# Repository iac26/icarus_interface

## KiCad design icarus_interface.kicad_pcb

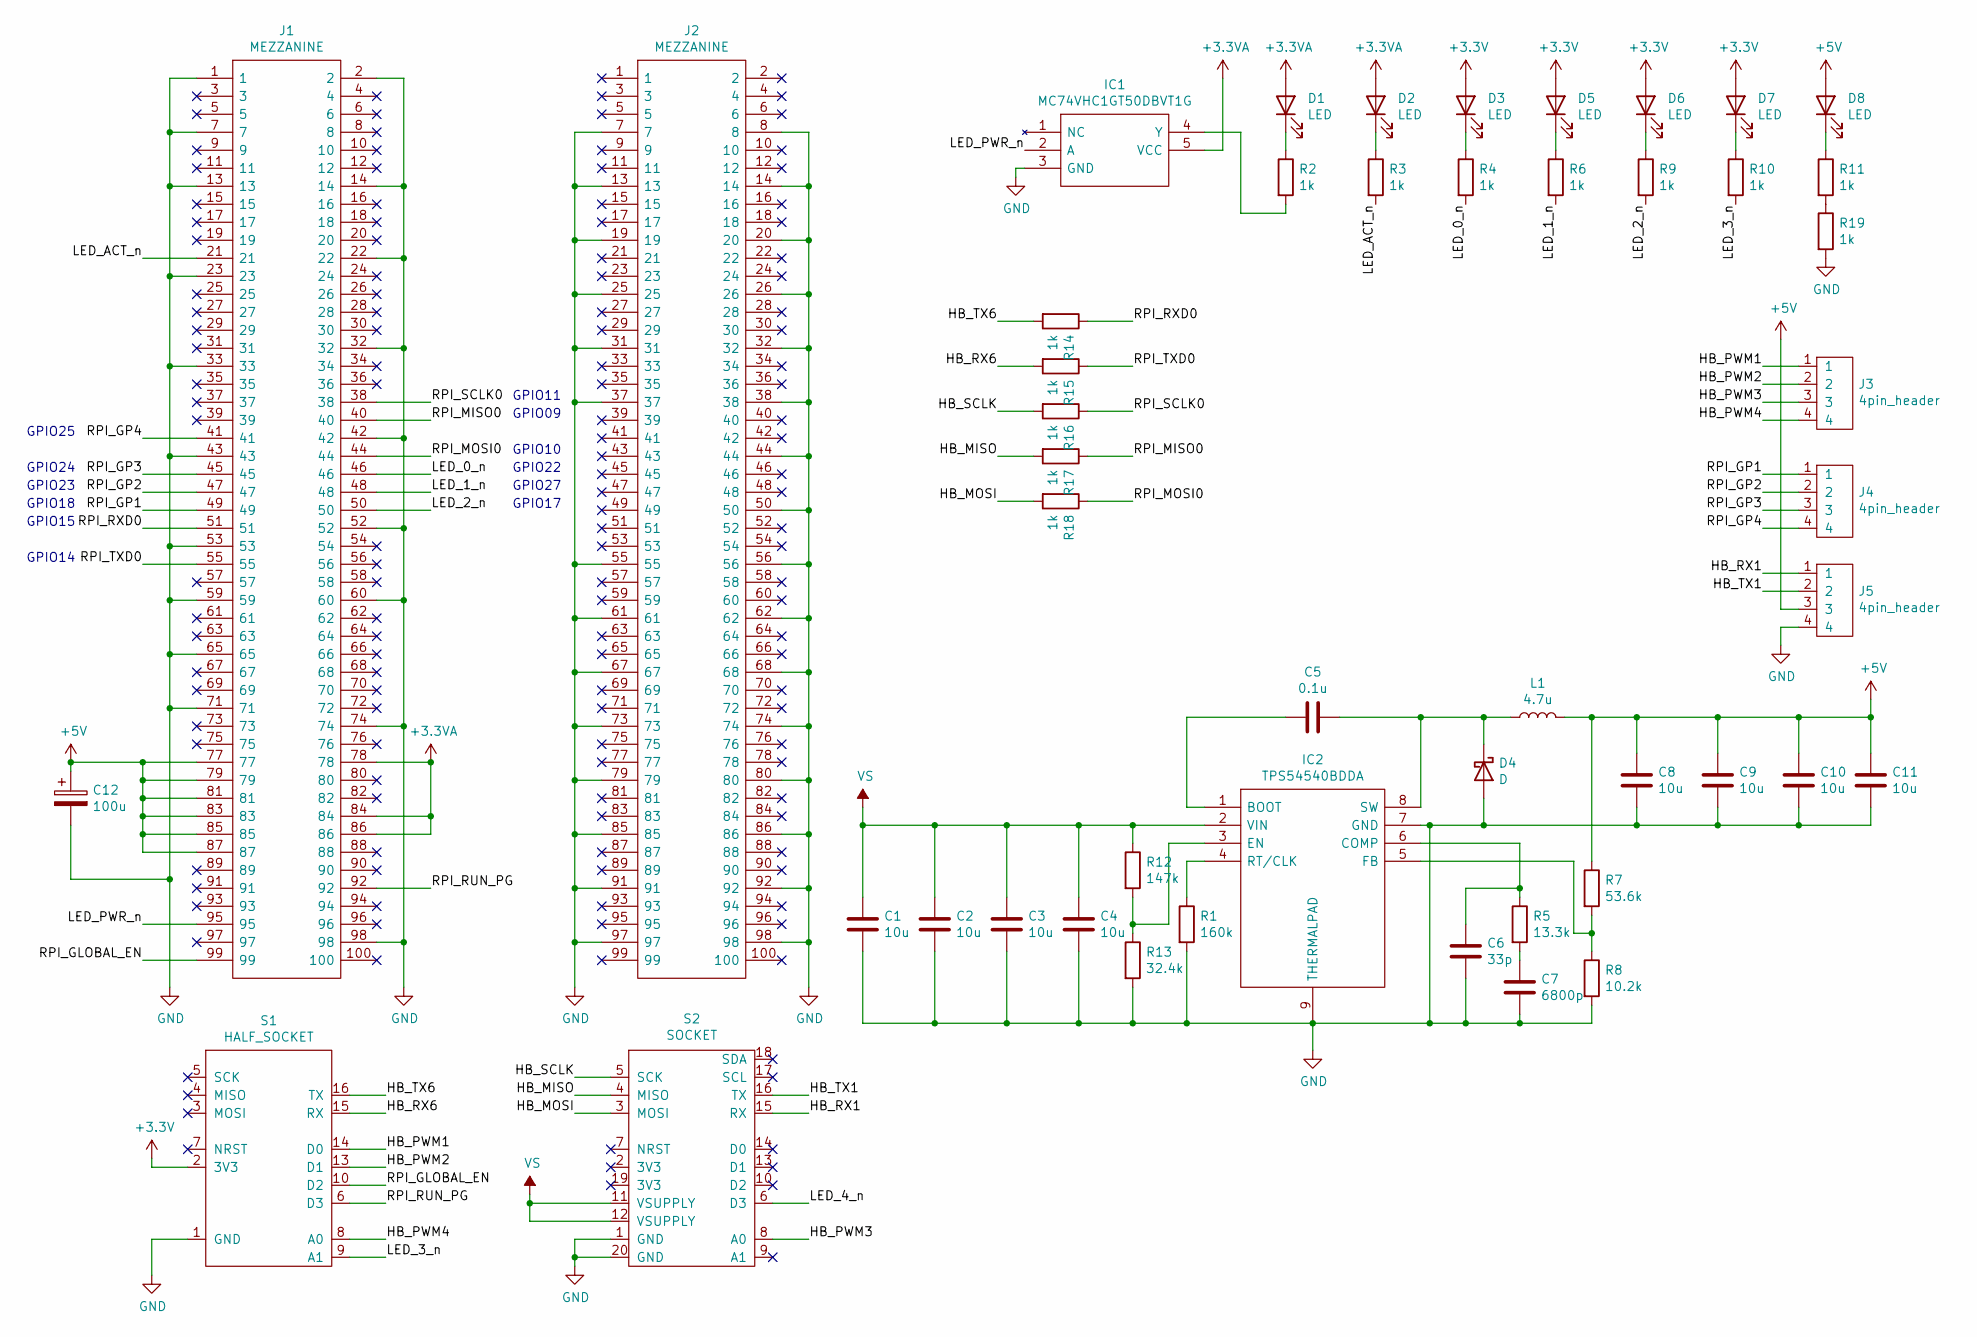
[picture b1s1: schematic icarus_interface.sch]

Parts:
C1, C2, C3, C4, C8, C9, C10, C11: 10u; C_1206_3216Metric
C5: 0.1u; C_1206_3216Metric
C6: 33p; C_0402_1005Metric
C7: 6800p; C_0402_1005Metric
C12: 100u; CP_EIA-3528-21_Kemet-B
D1, D2, D3, D5, D6, D7, D8: LED; LED_0603_1608Metric
D4: D; POWERDIODE
IC1: MC74VHC1GT50DBVT1G; SOT65P210X110-5N; Mouser Part Number 863-MC74VHC1GT50DBVG
IC2: TPS54540BDDA; TPS5454; Mouser Part Number 595-TPS54540BDDA
J1, J2: MEZZANINE; Mouser Part Number 798-DF40HC30100DS451
J3, J4, J5: 4pin_header; PinHeader_1x04_P2.54mm_Vertical
L1: 4.7u; L_Bourns_SRN6045TA
R1: 160k; R_0805_2012Metric
R2, R3, R4, R6, R9, R10, R11, R14, R15, R16, R17, R18, R19: 1k; R_0805_2012Metric
R5: 13.3k; R_0805_2012Metric
R7: 53.6k; R_0805_2012Metric
R8: 10.2k; R_0805_2012Metric
R12: 147k; R_0805_2012Metric
R13: 32.4k; R_0805_2012Metric
S1: HALF_SOCKET; half_socket
S2: SOCKET; Socket

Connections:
+3.3VA: D1.2 (A), D2.2 (A), IC1.5 (VCC), J1.78, J1.84, J1.86
+3V3: D3.2 (A), D5.2 (A), D6.2 (A), D7.2 (A), S1.2 (3V3)
+5V: C8.1, C9.1, C10.1, C11.1, C12.1, D8.2 (A), J1.77, J1.79, J1.81, J1.83, J1.85, J1.87, J5.3, L1.2, R7.1
/HB_MISO: R17.2, S2.4 (MISO)
/HB_MOSI: R18.2, S2.3 (MOSI)
/HB_PWM1: J3.1, S1.14 (D0)
/HB_PWM2: J3.2, S1.13 (D1)
/HB_PWM3: J3.3, S2.8 (A0)
/HB_PWM4: J3.4, S1.8 (A0)
/HB_RX1: J5.1, S2.15 (RX)
/HB_RX6: R15.2, S1.15 (RX)
/HB_SCLK: R16.2, S2.5 (SCK)
/HB_TX1: J5.2, S2.16 (TX)
/HB_TX6: R14.2, S1.16 (TX)
/LED_0_n: J1.46, R4.2
/LED_1_n: J1.48, R6.2
/LED_2_n: J1.50, R9.2
/LED_3_n: R10.2, S1.9 (A1)
/LED_4_n: S2.6 (D3)
/LED_ACT_n: J1.21, R3.2
/LED_PWR_n: IC1.2 (A), J1.95
/RPI_GLOBAL_EN: J1.99, S1.10 (D2)
/RPI_GP1: J1.49, J4.1
/RPI_GP2: J1.47, J4.2
/RPI_GP3: J1.45, J4.3
/RPI_GP4: J1.41, J4.4
/RPI_MISO0: J1.40, R17.1
/RPI_MOSI0: J1.44, R18.1
/RPI_RUN_PG: J1.92, S1.6 (D3)
/RPI_RXD0: J1.51, R14.1
/RPI_SCLK0: J1.38, R16.1
/RPI_TXD0: J1.55, R15.1
GND: C1.2, C2.2, C3.2, C4.2, C6.2, C7.2, C8.2, C9.2, C10.2, C11.2, C12.2, D4.2 (A), IC1.3 (GND), IC2.7 (GND), IC2.9 (THERMALPAD), J1.1, J1.2, J1.7, J1.13, J1.14, J1.22, J1.23, J1.32, J1.33, J1.42, J1.43, J1.52, J1.53, J1.59, J1.60, J1.65, J1.71, J1.74, J1.98, J2.7, J2.8, J2.13, J2.14, J2.19, J2.20, J2.25, J2.26, J2.31, J2.32, J2.37, J2.38, J2.44, J2.50, J2.55, J2.56, J2.61, J2.62, J2.67, J2.68, J2.73, J2.74, J2.79, J2.80, J2.85, J2.86, J2.91, J2.92, J2.97, J2.98, J5.4, R1.2, R8.2, R13.2, R19.2, S1.1 (GND), S2.1 (GND), S2.20 (GND)
unnamed: C5.1, D4.1 (K), IC2.8 (SW), L1.1
unnamed: C5.2, IC2.1 (BOOT)
unnamed: C6.1, IC2.6 (COMP), R5.1
unnamed: C7.1, R5.2
unnamed: D1.1 (K), R2.1
unnamed: D2.1 (K), R3.1
unnamed: D3.1 (K), R4.1
unnamed: D5.1 (K), R6.1
unnamed: D6.1 (K), R9.1
unnamed: D7.1 (K), R10.1
unnamed: D8.1 (K), R11.1
unnamed: IC1.4 (Y), R2.2
unnamed: IC2.3 (EN), R12.2, R13.1
unnamed: IC2.4 (RT/CLK), R1.1
unnamed: IC2.5 (FB), R7.2, R8.1
unnamed: R11.2, R19.1
VS: C1.1, C2.1, C3.1, C4.1, IC2.2 (VIN), R12.1, S2.11 (VSUPPLY), S2.12 (VSUPPLY)

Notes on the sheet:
GPIO25
GPIO24
GPIO23
GPIO18
GPIO15
GPIO14
GPIO11
GPIO09
GPIO10
GPIO22
GPIO27
GPIO17

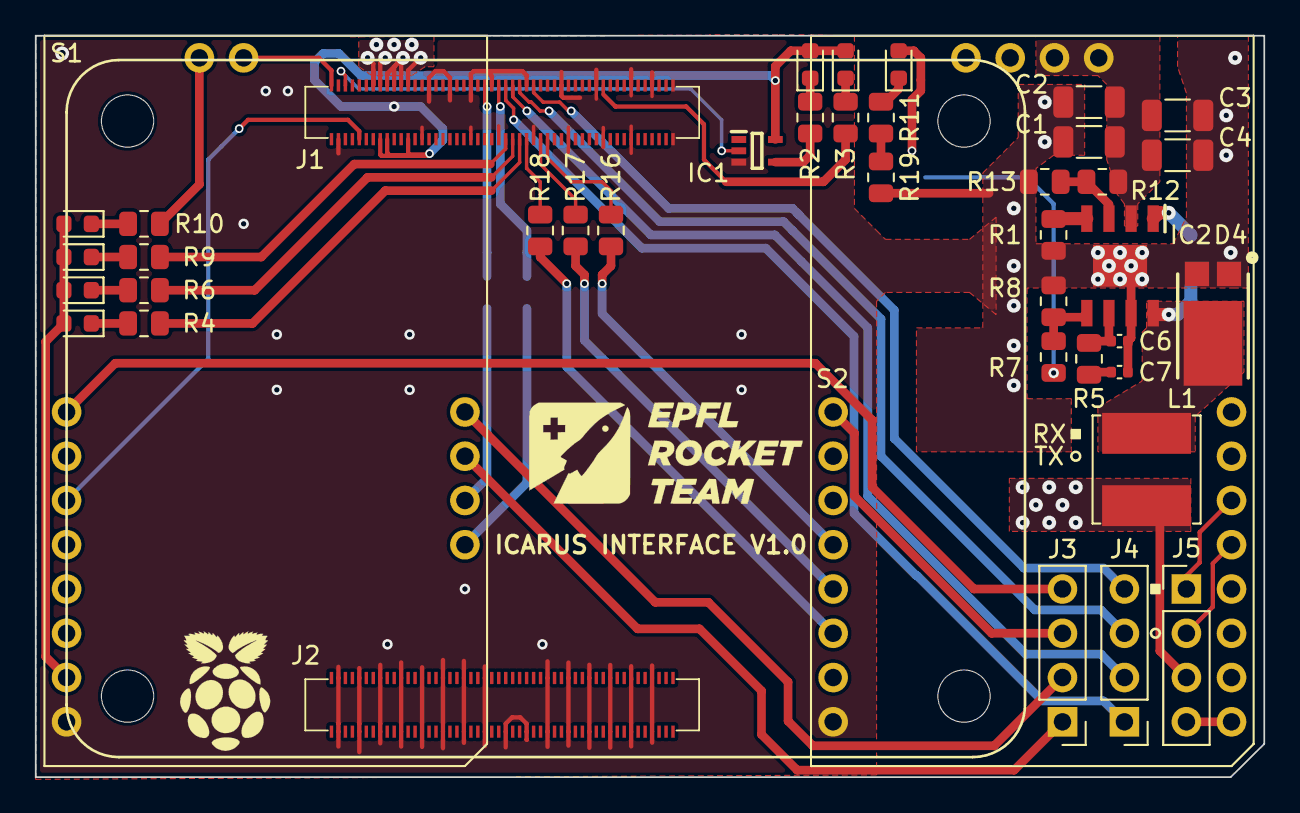
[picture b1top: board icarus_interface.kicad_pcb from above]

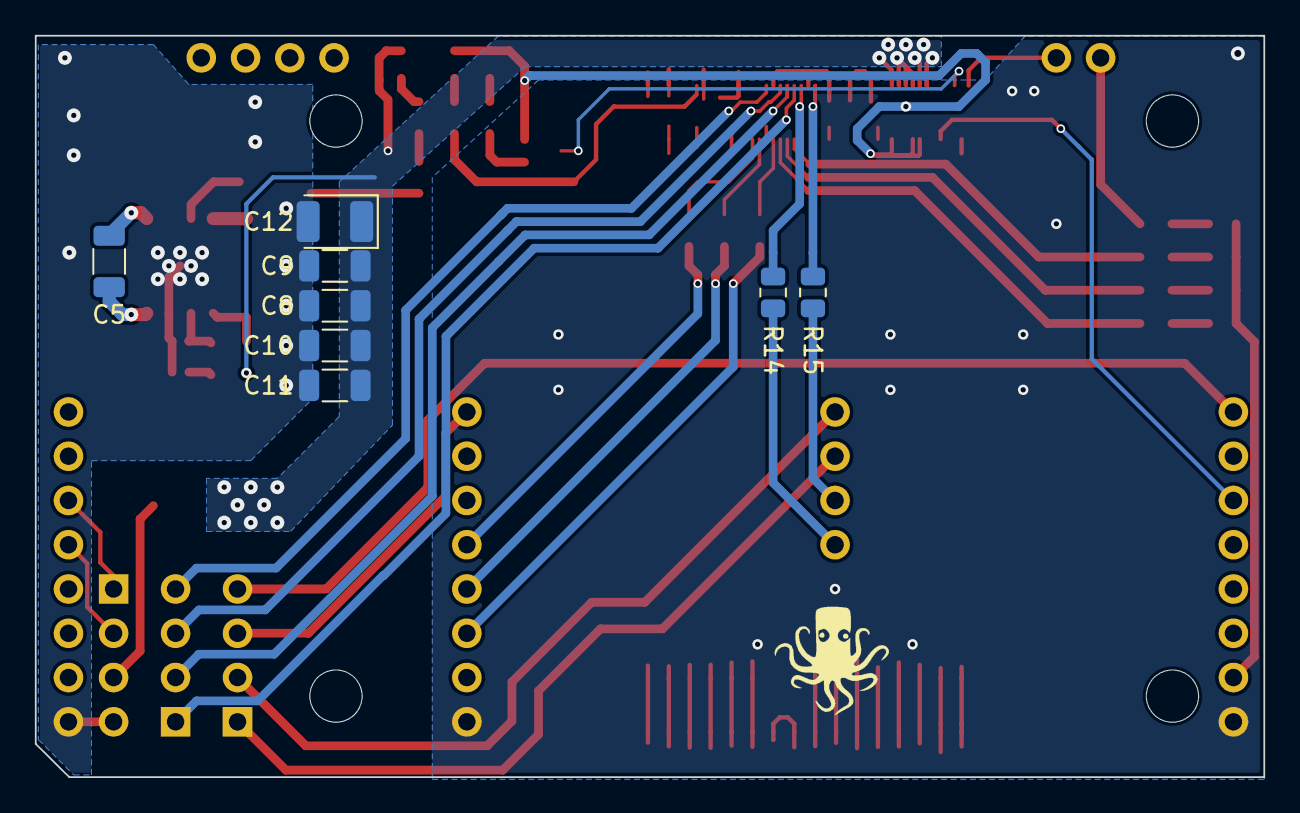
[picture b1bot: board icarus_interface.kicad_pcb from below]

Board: 2 copper layers, 70.5 x 42.5 mm, 49 parts (8 on the bottom side), 49 nets.

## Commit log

2021-04-07 quick modifs
2021-04-09 sync
